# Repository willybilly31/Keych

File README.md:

# Keych

Keych is a small wearable electronics project built around an ESP32-C3. It features a small OLED display and physical buttons, all powered by a rechargeable LiPo battery.

## Features

* ESP32-C3 SuperMini
* SSD1306 OLED display
* 2 × 6×6 mm push buttons
* 3.7V LiPo battery
* Buck converter
* Battery connector

## Hardware

The ESP32-C3 handles the main processing and controls the OLED display and buttons. The LiPo battery provides portable power, with the buck converter regulating the voltage for the electronics.

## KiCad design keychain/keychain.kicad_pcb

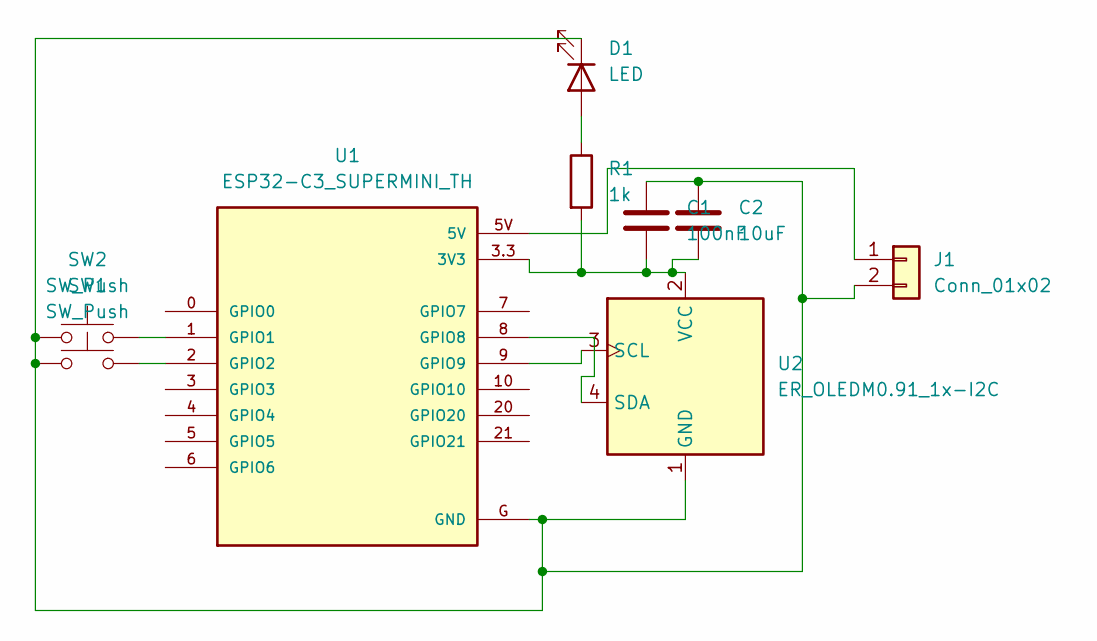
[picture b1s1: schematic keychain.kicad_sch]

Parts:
C1: 100nF; C_0805_2012Metric
C2: 10uF; C_0805_2012Metric
D1: LED; LED_0805_2012Metric
J1: Conn_01x02; JST_PH_S2B-PH-K_1x02_P2.00mm_Horizontal
R1: 1k; R_0805_2012Metric
SW1, SW2: SW_Push; SW_PUSH_6mm
U1: ESP32-C3_SUPERMINI_TH; MODULE_ESP32-C3_SUPERMINI_TH
U2: ER_OLEDM0.91_1x-I2C; SSD1306_0.96_Oled

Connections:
unnamed: D1.2 (A), R1.1
unnamed: C1.1, C2.1, D1.1 (K), J1.2, SW1.1, SW2.1, U1.G (GND), U2.1 (GND)
unnamed: J1.1, U1.5V
unnamed: C1.2, C2.2, R1.2, U1.3.3 (3V3), U2.2 (VCC)
unnamed: SW2.2, U1.1 (GPIO1)
unnamed: SW1.2, U1.2 (GPIO2)
unnamed: U1.8 (GPIO8), U2.4 (SDA)
unnamed: U1.9 (GPIO9), U2.3 (SCL)

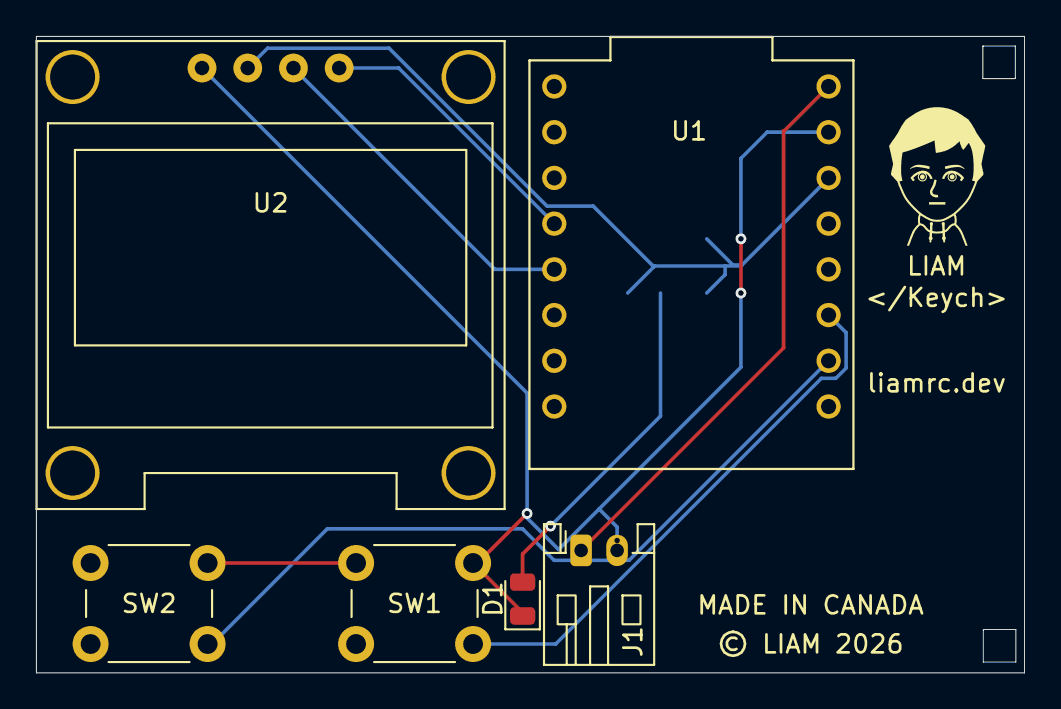
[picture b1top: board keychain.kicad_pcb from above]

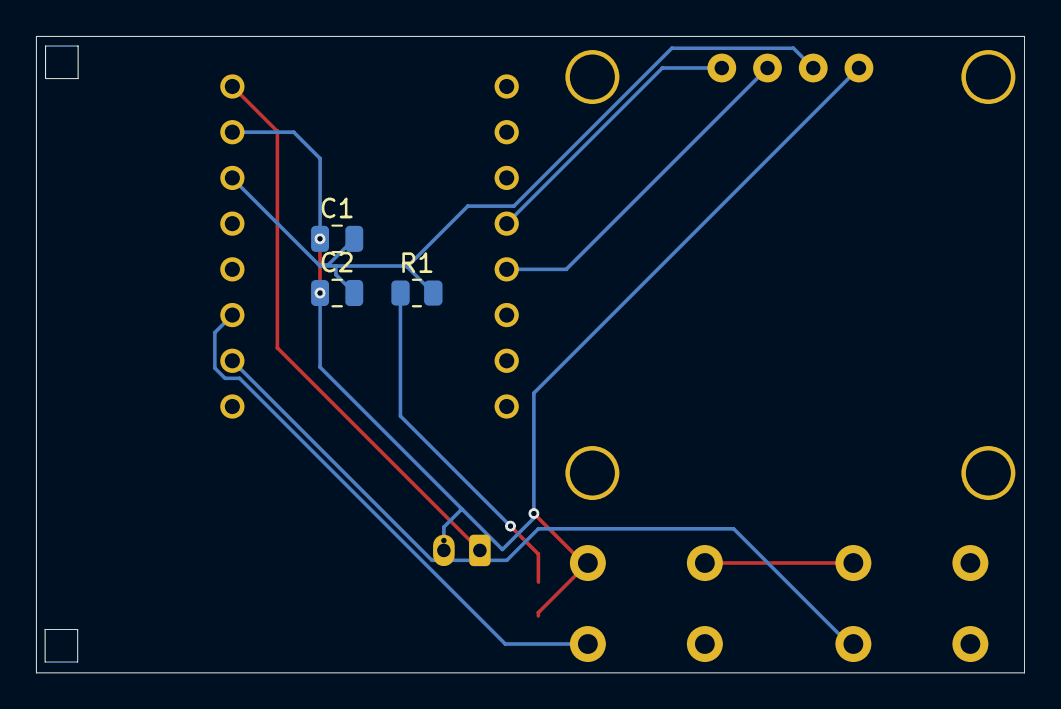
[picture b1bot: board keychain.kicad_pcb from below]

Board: 2 copper layers, 54.9 x 35.4 mm, 9 parts (3 on the bottom side), 8 nets.

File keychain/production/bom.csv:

Designator,Footprint,Quantity,Value,LCSC Part #
C1,0805,1,100nF,
C2,0805,1,10uF,
D1,0805,1,LED,
J1,JST_PH_S2B-PH-K_1x02_P2.00mm_Horizontal,1,Conn_01x02,
R1,0805,1,1k,
"SW1, SW2",SW_PUSH_6mm,2,SW_Push,
U1,MODULE_ESP32-C3_SUPERMINI_TH,1,ESP32-C3_SUPERMINI_TH,
U2,SSD1306_0.96_Oled,1,ER_OLEDM0.91_1x-I2C,

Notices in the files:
keychain/keychain.kicad_pcb:
© LIAM 2026
